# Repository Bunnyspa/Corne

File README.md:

# Corne

[Corne](https://github.com/foostan/crkbd) V3 keyboard with various features to achieve:
- Low PCB print cost (i.e. reversibility)
- Easy hand soldering
- Symmetry

## Warning
I have **NOT** tested the PH 2.0mm battery connector yet. Let me know if it works.

## Features
- MX, Choc V1, and Choc V2 switch support
- Wired and wireless support
- Reversible PCB
- Through-hole and SMD diode support
- Default pinouts (i.e. you can use the default QMK or ZMK firmware)

### Wired
- OLED display support
- 6-pin USB-C as keyboard link

### Wireless
- nice!view support
- PH 2.0mm (and just plain through-hole pads) for battery
- Power switch at the north side, either front or back (your choice)

## Design Choice Explanation

### Keyboard link
- The 6-pin version is used for easier hand soldering
- TRRS is not used due to the lack of symmetry

### OLED pinout location is slightly to the left
- To counter the OLEDs having the display area slightly to the right
- To overlap nice!view pinout location

## Jumper Soldering

The images above show the backside.

To support the PCB reversibility, jumper pads are added (pretty much everywhere). The through-hole solder pads themselves are not connected to anything, so you need to connect jumpers together where you solder the pads.

### Display

For nice!view, you must connect the upper jumper pad (right side in the picture).

For 4-pin I2C OLEDs, you must connect the lower jumper pad (left side in the picture).

## IRL Testing
The PCB has been tested with these parts (per side):
- Solder PCB from JLCPCB
- nice!nano
- nice!view 3rd-party alternative (Taobao)
- 750mAh battery (to the plain through-hole pads)
- SPDT switch for power switch
- Tactile switch for reset switch
- Choc V2 switches
- 1N4148W SMD diodes
- Default ZMK Corne + nice!view firmware

I also tried Pro Micro + OLED combo with QMK, and they worked fine. (I did not fully build the Corne for this one. Just the MCU and the display.)

I have **NOT** tested the PH 2.0mm battery connector yet. Let me know if it works.

## Warning for Custom Firmware
The bottom 4 of MCU board pinouts do not support reversibility (hence no jumper pads). If your custom firmware uses these pins, you should configure pinouts for each side properly.

## PCB Preview
| Solder  | Hotswap |
| - | - |
|   |   |

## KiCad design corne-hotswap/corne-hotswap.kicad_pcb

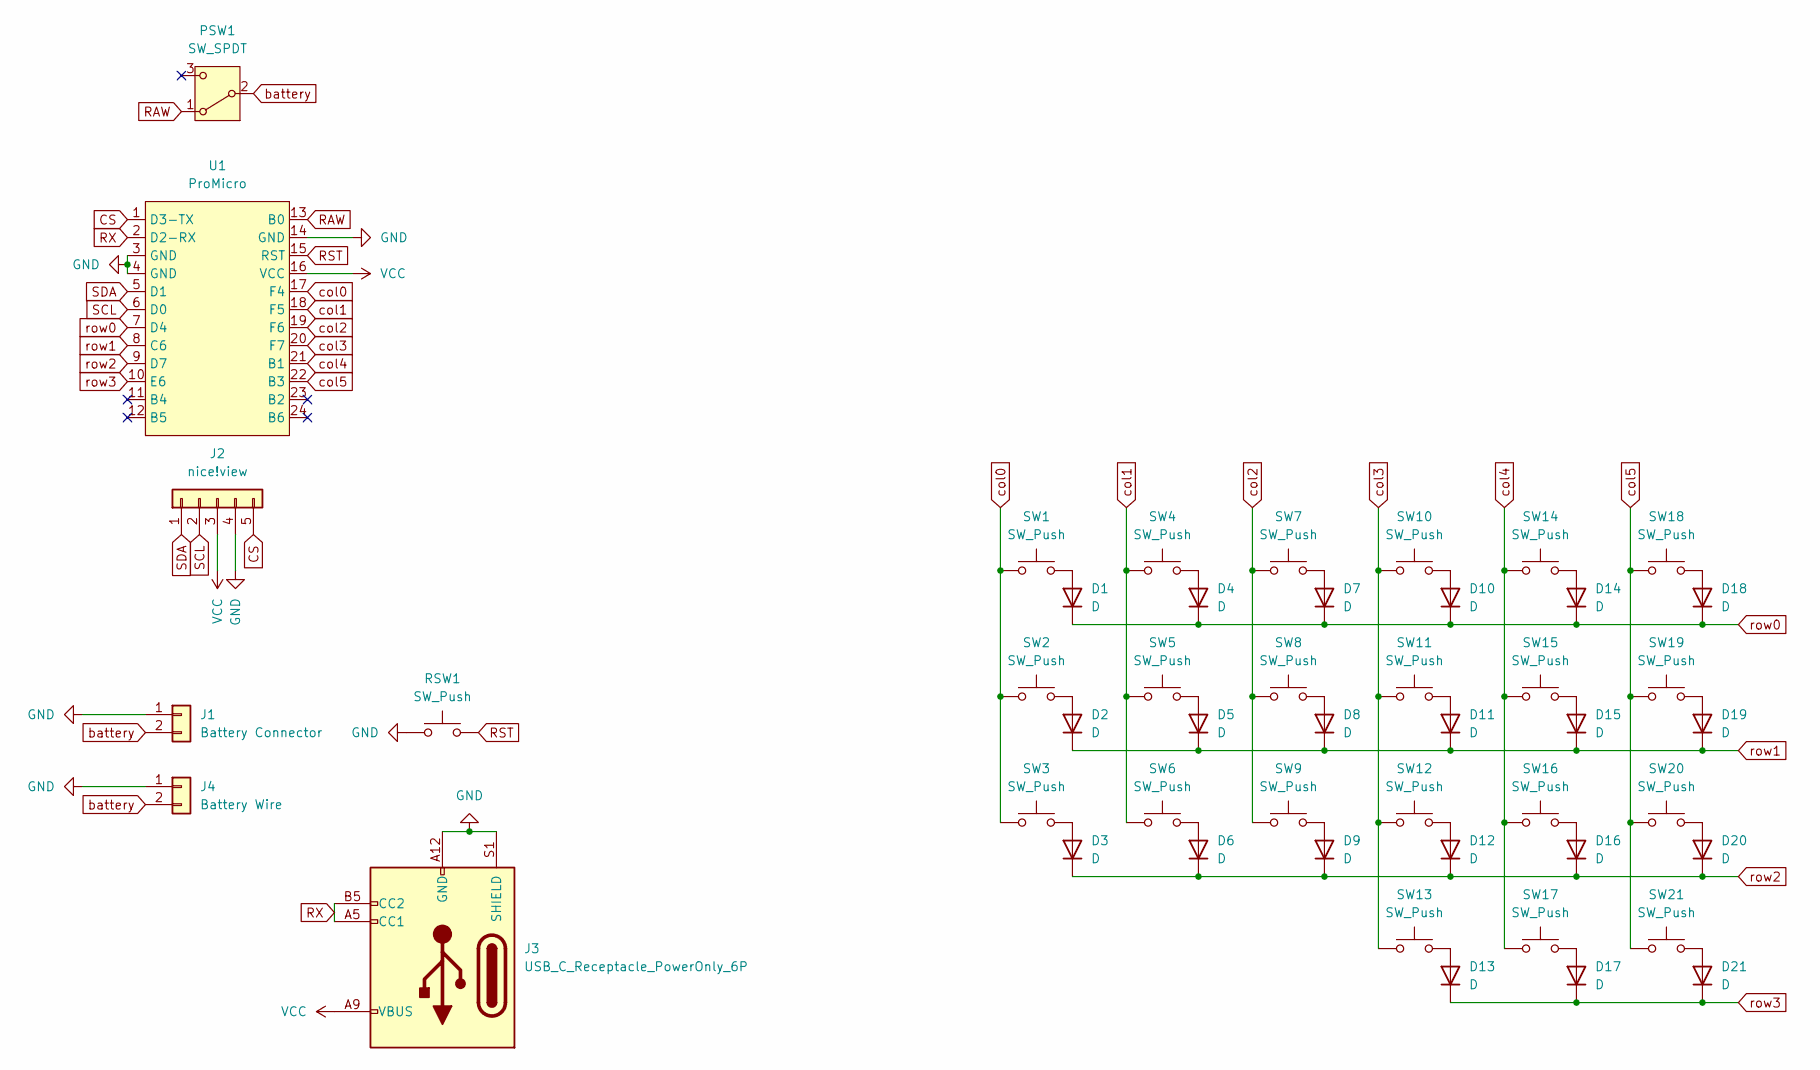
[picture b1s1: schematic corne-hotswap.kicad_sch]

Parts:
D1, D2, D3, D4, D5, D6, D7, D8, D9, D10, D11, D12, D13, D14, D15, D16, D17, D18, D19, D20, D21: D; Diode-Reversible
J1: Battery Connector; JST_PH_S2B-PH-K_1x02_P2.00mm_Horizontal
J2: nice!view; Nice_View
J3: USB_C_Receptacle_PowerOnly_6P; USB_C_Receptacle_GCT_USB4125-xx-x_6P_TopMnt_Horizontal
J4: Battery Wire
PSW1: SW_SPDT; SW_SPDT_PCM12
RSW1: SW_Push; SW_PUSH_1P1T_6x3.5mm_H4.3_APEM_MJTP1243
SW1, SW2, SW3, SW4, SW5, SW6, SW7, SW8, SW9, SW10, SW11, SW12, SW13, SW14, SW15, SW16, SW17, SW18, SW19, SW20, SW21: SW_Push; Switch-MX_ChocV2-Reversible-Hotswap
U1: ProMicro; Pro_Micro-Reversible

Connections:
CS: J2.5, U1.1 (D3-TX)
GND: J1.1, J2.4, J3.A12 (GND), J3.B12 (GND), J3.S1 (SHIELD), J4.1, RSW1.1, U1.3 (GND), U1.4 (GND), U1.14 (GND)
unnamed: D1.2 (A), SW1.2
unnamed: D2.2 (A), SW2.2
unnamed: D3.2 (A), SW3.2
unnamed: D4.2 (A), SW4.2
unnamed: D5.2 (A), SW5.2
unnamed: D6.2 (A), SW6.2
unnamed: D7.2 (A), SW7.2
unnamed: D8.2 (A), SW8.2
unnamed: D9.2 (A), SW9.2
unnamed: D10.2 (A), SW10.2
unnamed: D11.2 (A), SW11.2
unnamed: D12.2 (A), SW12.2
unnamed: D13.2 (A), SW13.2
unnamed: D14.2 (A), SW14.2
unnamed: D15.2 (A), SW15.2
unnamed: D16.2 (A), SW16.2
unnamed: D17.2 (A), SW17.2
unnamed: D18.2 (A), SW18.2
unnamed: D19.2 (A), SW19.2
unnamed: D20.2 (A), SW20.2
unnamed: D21.2 (A), SW21.2
RAW: PSW1.1 (A), U1.13 (B0)
RST: RSW1.2, U1.15 (RST)
RX: J3.A5 (CC1), J3.B5 (CC2), U1.2 (D2-RX)
SCL: J2.2, U1.6 (D0)
SDA: J2.1, U1.5 (D1)
VCC: J2.3, J3.A9 (VBUS), J3.B9 (VBUS), U1.16 (VCC)
battery: J1.2, J4.2, PSW1.2 (B)
col0: SW1.1, SW2.1, SW3.1, U1.17 (F4)
col1: SW4.1, SW5.1, SW6.1, U1.18 (F5)
col2: SW7.1, SW8.1, SW9.1, U1.19 (F6)
col3: SW10.1, SW11.1, SW12.1, SW13.1, U1.20 (F7)
col4: SW14.1, SW15.1, SW16.1, SW17.1, U1.21 (B1)
col5: SW18.1, SW19.1, SW20.1, SW21.1, U1.22 (B3)
row0: D1.1 (K), D4.1 (K), D7.1 (K), D10.1 (K), D14.1 (K), D18.1 (K), U1.7 (D4)
row1: D2.1 (K), D5.1 (K), D8.1 (K), D11.1 (K), D15.1 (K), D19.1 (K), U1.8 (C6)
row2: D3.1 (K), D6.1 (K), D9.1 (K), D12.1 (K), D16.1 (K), D20.1 (K), U1.9 (D7)
row3: D13.1 (K), D17.1 (K), D21.1 (K), U1.10 (E6)

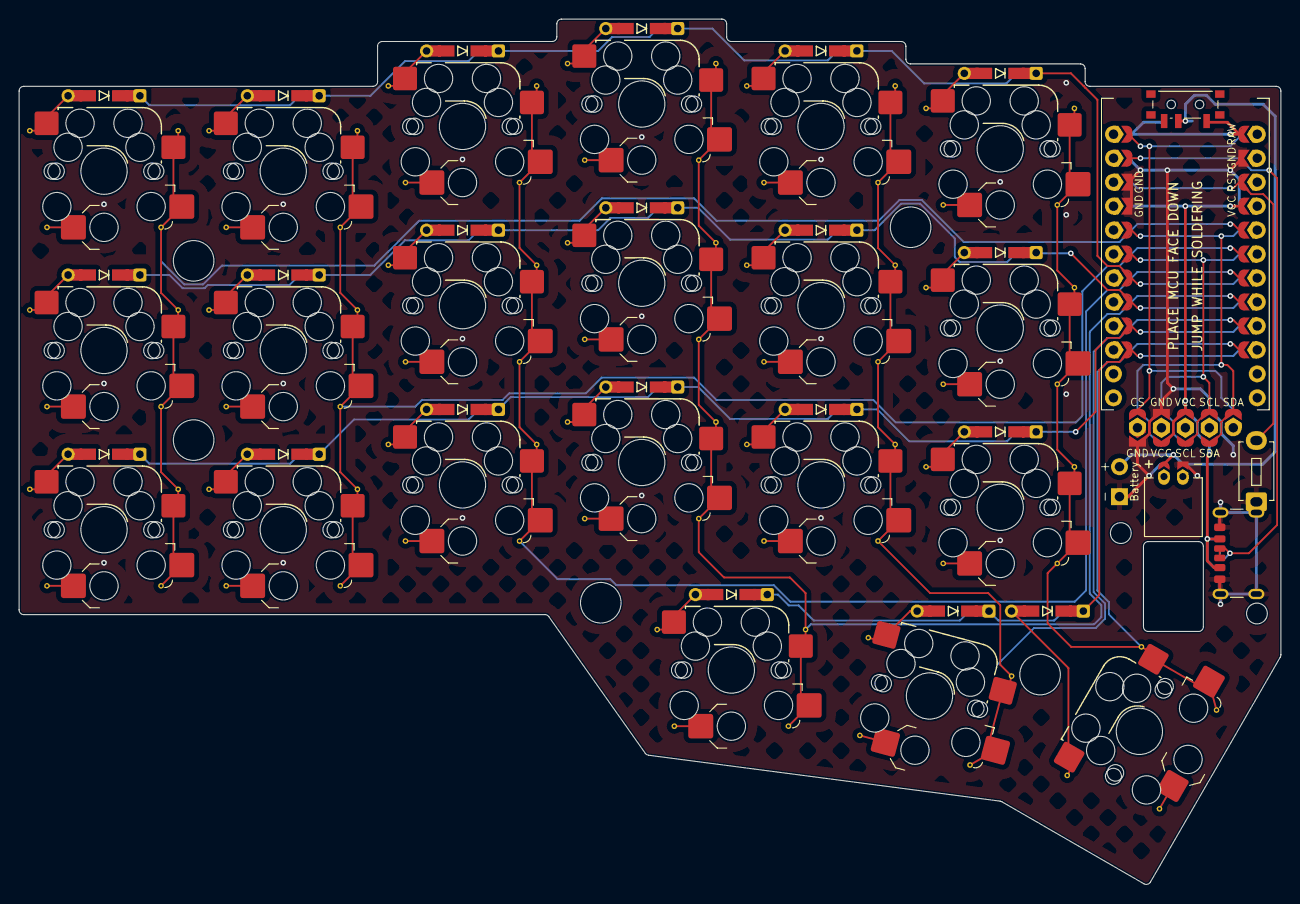
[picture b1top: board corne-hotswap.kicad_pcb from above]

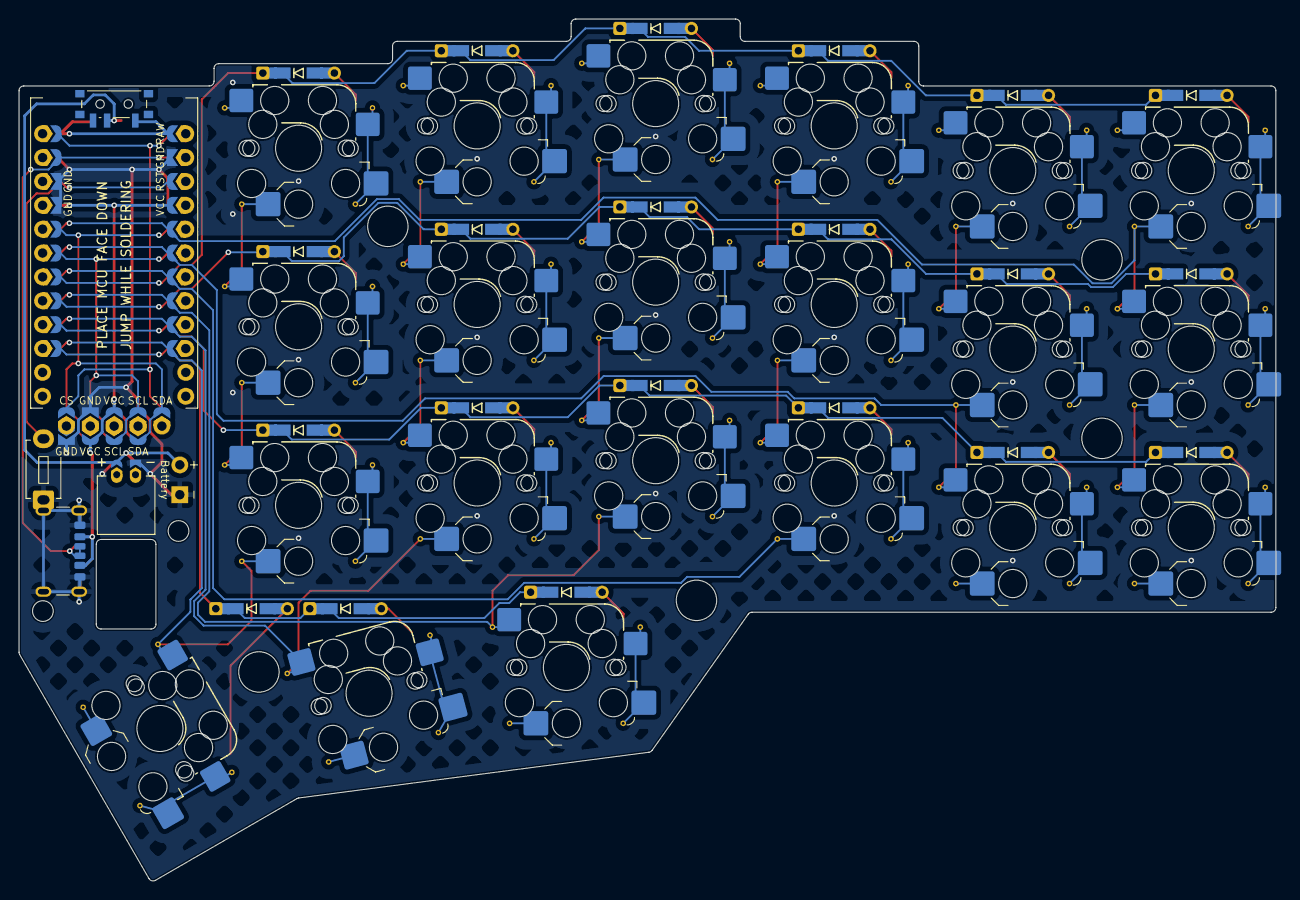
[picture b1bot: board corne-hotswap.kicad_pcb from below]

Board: 2 copper layers, 133.8 x 91.7 mm, 49 parts (22 on the bottom side), 40 nets.

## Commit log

2025-03-20 add libraries
2025-03-21 rename symbol library
2025-03-21 rename libraries
2025-03-21 more footprints
2025-03-21 footprint assign
2025-03-21 remove wrong footprint from reset switch
2025-03-21 Move libraries
2025-03-21 Update lib
2025-03-21 pcb edit
2025-03-22 edit
2025-03-22 rename
2025-03-22 add solder version
2025-03-22 move future project to wip dir
2025-03-22 wiring
2025-03-23 more wiring and DRC
2025-03-23 move niceview jump pads
2025-03-24 jump pads edit
2025-03-24 More jump pads
2025-03-24 add bridge for wired
2025-03-25 fix 3d model path
2025-03-25 edit pcb
2025-03-25 Add measurements
2025-03-25 add fillet to corners
2025-03-25 add resource dir
2025-03-25 add edge cut guide line
2025-03-26 silkscreen label and description change
    Labels now indicate jumper pads. Description is changed to clarify what labels are indicating.
2025-03-26 add battery wire pads
2025-03-26 Add batt silks
2025-03-26 update copper fill
2025-03-26 change after running fab toolkit
2025-03-26 small track change
2025-03-26 add wip hotswap
2025-03-26 diode footprint edit
2025-03-26 hotswap switch footprint change
2025-03-26 Revert "hotswap switch footprint change"
    This reverts commit 98a31c7d3c40b55c292cbbfedf432d9a1d5aac7c.
2025-03-26 column wiring
2025-03-27 rename hotswap directory
2025-03-27 add preview images
2025-03-27 change readme
2025-04-01 add netclass pattern
2025-04-01 move cs to default pinout
2025-04-01 major edit
2025-04-02 modularization
2025-04-02 new design (using module)
2025-04-02 wiring update
2025-04-03 minor wiring update
2025-04-03 module wiring update
2025-04-04 pad shape change
2025-04-04 picture update
2025-04-11 edit jumpers and texts
2025-04-24 edit display footprint
2025-08-15 instruction and battery jst hole update
2025-08-22 Update images
2025-08-22 Edit to reflect current version label
2025-08-22 minor fix to readme
